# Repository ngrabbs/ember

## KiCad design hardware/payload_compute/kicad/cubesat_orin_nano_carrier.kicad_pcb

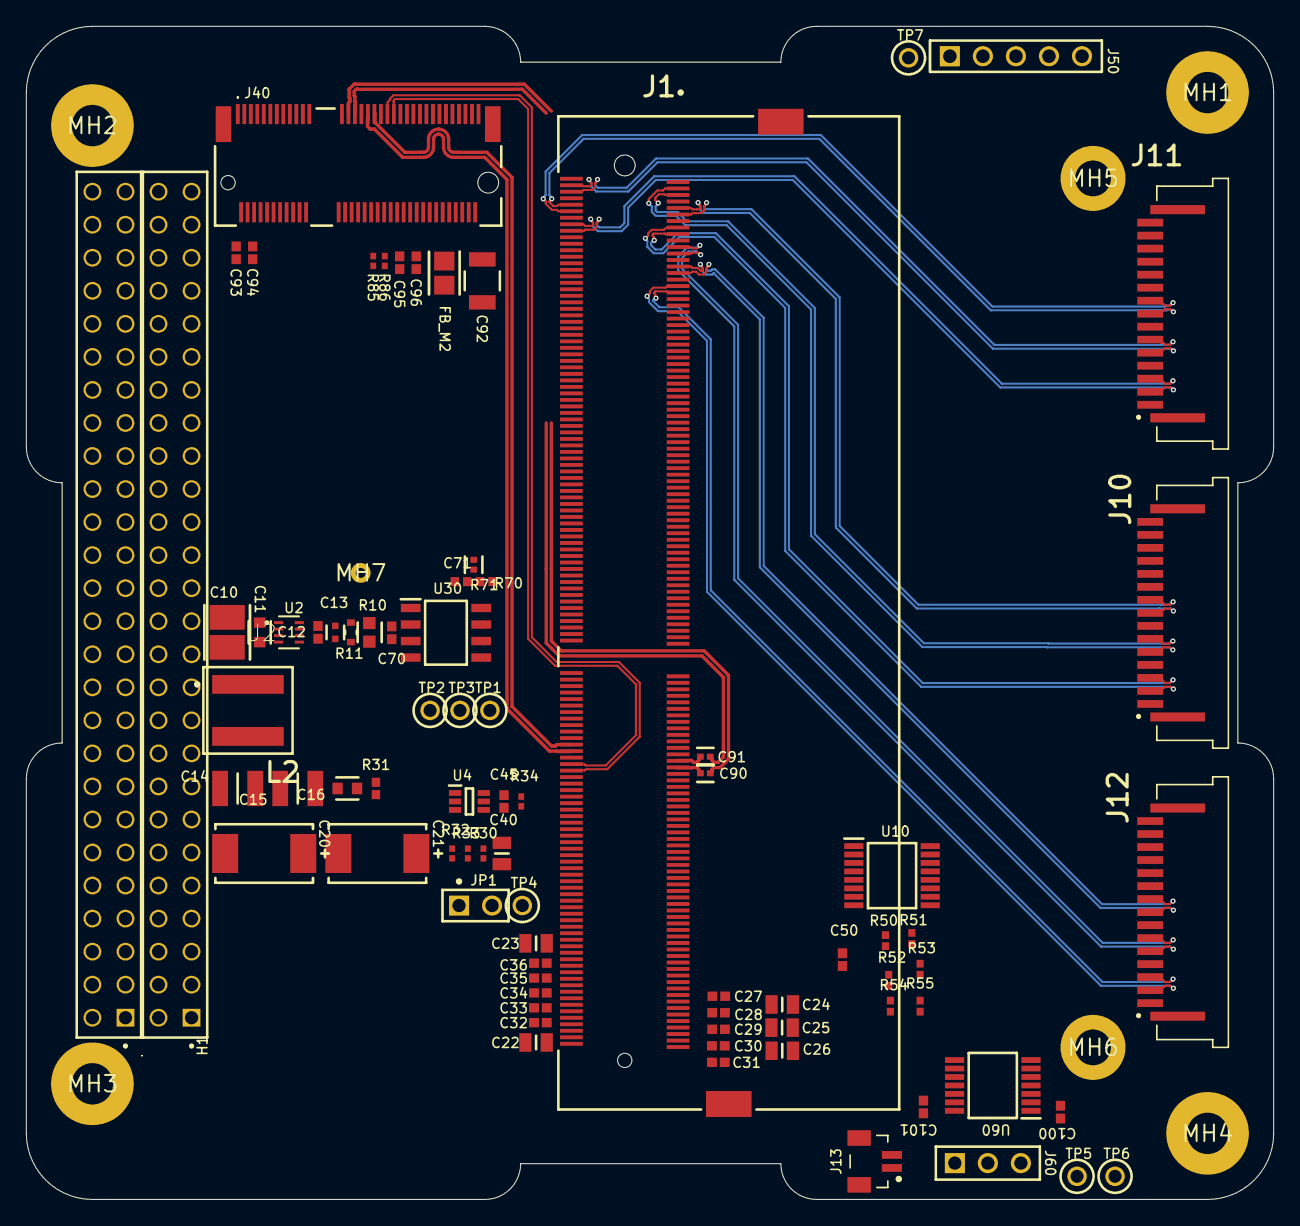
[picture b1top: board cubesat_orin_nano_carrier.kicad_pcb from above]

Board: 4 copper layers, 95.9 x 90.2 mm, 87 parts (0 on the bottom side), 86 nets.

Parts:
C10: GCM32EC7YA106KA03L; FP-GCM32E-0_3-IPC_B
C11, C16: C14663; FP-CC0603-DA-MFG
C12, C27, C28, C29, C30, C31, C32, C33, C34, C35, C36, C45, C50, C70, C93, C94, C95, C96, C100, C101: CL05B104KO5NNNC; CAPC1050X55X23ML05T13
C13: CC0402KRX7R7BB333; FP-CC0402-MFG
C14, C15: CL32A226KAJNNNE; CAPC3225X270N
C20, C21: TAJD107K020RNJ; FP-TAJD-MFG
C22, C23, C24, C25, C26, C40: CL21B106KPQNNNE; CAPC2012X140N
C71: CL05B472KB5NNNC; FP-CL967-IPC_C
C90, C91: CL05B224KO5NNNC; FP-CL549-IPC_C
C92: GRM32ER71E226KE15L; FP-GRM32E-0_3-0_2-MFG
FB_M2: BLM21PG600SN1D; FP-BLM21-0_2-t0_85-e0_5-d-IPC_A
H1, H2: ESQ-126-39-G-D; SAMTEC_ESQ-126-39-G-D
J1: 2309413-1; FP-2309413-1-MFG
J10, J11, J12: SFW15R-2STE1LF; AMPHENOL_SFW15R-2STE1LF
J13: BM02B-SRSS-TB(LF)(SN); BM02B-SRSS-TB_LF_SN_MFG
J40: MDT420E01001
J50: SSW-105-01-T-S; SMTC-SSW-105-01-X-S
J60: TSW-103-07-F-S; SMTC-TSW-103-07-X-S
JP1: 68000-102HLF; AMPH-68000-102HLF_V
L2: 74439346068; WE-XHMI_6060
MH1, MH2, MH3, MH4: M3_PC104_3.18mm
MH5, MH6: M2.5_module_2.75mm
MH7: Tooling_0.762mm
R10: CRCW060352K3FKEA; FP-CRCW0603-e3-IPC_B
R11: SG73P1JTTD1002F; FP-SG73P1J-MFG
R30, R32, R33, R34, R85, R86: RC0402FR-0710KL; RESC1005X40X25LL05T10
R31: RC0402FR-0749K9L; RESC1005X40X25ML05T10
R50, R51, R52, R53, R54, R55: RC0402FR-074K7L; RESC1005X40X25NL05T10
R70, R71: RC0402FR-0760R4L; RESC1005X40X25ML05T10
TP1, TP2, TP3, TP4, TP5, TP6, TP7: 5003; KSTN-5003
U2: TPS62933FDRLR; SOT5X3-8_DRL_TEX
U4: 74LVC2G07GW,125; SOP65P210X110-6N
U10: PCA9546APW,118; SOP65P640X110-16N
U30: TCAN332GDR; SOIC127P600X175-8N
U60: TXB0104QPWRQ1; SOP65P640X120-14N

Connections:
+1V8_MOD: C45.2, C100.1, R32.2, R33.1, U4.5, U60.1
+3V3: C50.2, C70.2, C101.1, FB_M2.1, H2.27, H2.28, J10.15, J11.15, J12.15, R34.1, R50.2, R51.2, R52.2, R53.2, R54.2, R55.2, U10.16, U30.3, U60.8, U60.14
+3V3_M2: C92.1, C93.2, C94.2, C95.2, C96.2, FB_M2.2, R85.1, R86.1
+5V: H2.25, H2.26
+5V_ORIN: C14.1, C15.1, C16.1, C20.2, C21.2, C22.2, C23.2, C24.2, C25.2, C26.2, C27.2, C28.2, C29.2, C30.2, C31.2, C32.2, C33.2, C34.2, C35.2, C36.2, J1.251, J1.252, J1.253, J1.254, J1.255, J1.256, J1.257, J1.258, J1.259, J1.260, L2.2, R10.2, R30.1, R31.2
+5V_TEST: J50.1, TP7.1
CAM0_CLK_N: J1.10, J10.8
CAM0_CLK_P: J1.12, J10.9
CAM0_D0_N: J1.4, J10.5
CAM0_D0_P: J1.6, J10.6
CAM0_D1_N: J1.16, J10.2
CAM0_D1_P: J1.18, J10.3
CAM0_PWDN: J1.127, J10.11
CAM0_SCL: J10.13, R51.1, U10.5
CAM0_SDA: J10.14, R50.1, U10.4
CAM1_CLK_N: J1.9, J11.8
CAM1_CLK_P: J1.11, J11.9
CAM1_D0_N: J1.3, J11.5
CAM1_D0_P: J1.5, J11.6
CAM1_D1_N: J1.15, J11.2
CAM1_D1_P: J1.17, J11.3
CAM1_PWDN: J1.130, J11.11
CAM1_SCL: J11.13, R53.1, U10.7
CAM1_SDA: J11.14, R52.1, U10.6
CAM2_CLK_N: J1.28, J12.8
CAM2_CLK_P: J1.30, J12.9
CAM2_D0_N: J1.22, J12.5
CAM2_D0_P: J1.24, J12.6
CAM2_D1_N: J1.34, J12.2
CAM2_D1_P: J1.36, J12.3
CAM2_PWDN: J1.211, J12.11
CAM2_SCL: J12.13, R54.1, U10.10
CAM2_SDA: J12.14, R55.1, U10.9
CAM_I2C_SCL: J1.213, U10.14
CAM_I2C_SDA: J1.215, U10.15
CAM_TRIG_1V8: J1.128, J13.1
CAN_H: H1.51, R70.2, U30.7
CAN_L: H1.52, R71.1, U30.6
CAN_RX: J1.143, U30.4
CAN_TX: J1.145, U30.1
CLK_32K_OUT: J1.210, TP3.1
DBG_UART_RX_1V8: J1.205, TP6.1, U60.3
DBG_UART_RX_3V3: J60.3, U60.12
DBG_UART_TX_1V8: J1.203, TP5.1, U60.2
DBG_UART_TX_3V3: J60.2, U60.13
FRC_RCVRY_N: J1.214, JP1.1, R33.2
GND: C10.2, C11.2, C13.2, C14.2, C15.2, C16.2, C20.1, C21.1, C22.1, C23.1, C24.1, C25.1, C26.1, C27.1, C28.1, C29.1, C30.1, C31.1, C32.1, C33.1, C34.1, C35.1, C36.1, C40.1, C45.1, C50.1, C70.1, C71.2, C92.2, C100.2, C101.2, H2.29, H2.30, H2.31, H2.32, J1.1, J1.2, J1.7, J1.8, J1.13, J1.14, J1.19, J1.20, J1.25, J1.26, J1.31, J1.32, J1.37, J1.38, J1.43, J1.44, J1.49, J1.50, J1.55, J1.56, J1.61, J1.62, J1.67, J1.68, J1.73, J1.74, J1.79, J1.80, J1.85, J1.86, J1.102, J1.107, J1.119, J1.125, J1.129, J1.132, J1.135, J1.138, J1.141, J1.144, J1.146, J1.147, J1.152, J1.153, J1.158, J1.159, J1.164, J1.165, J1.170, J1.171, J1.176, J1.177, J1.200, J1.201, J1.217, J1.231, J1.241, J1.242, J1.243, J1.244, J1.245, J1.246, J1.247, J1.248, J1.249, J1.250, J10.1, J10.4, J10.7, J10.10, J10.S1, J10.S2, J11.1, J11.4, J11.7, J11.10, J11.S1, J11.S2, J12.1, J12.4, J12.7, J12.10, J12.S1, J12.S2, J13.2, J13.3, J13.4, J40.76, J40.77, J50.5, J60.1, JP1.2, MH1.3, MH2.4, MH3.1, MH4.2, MH5.5, MH6.5, R11.1, R31.1, U2.4, U4.2, U10.1, U10.2, U10.8, U10.13, U30.2, U60.7
I2C_SCL: H1.43, J1.185
I2C_SDA: H1.41, J1.187
M2_PCIE1_TX0_N: C91.2, J40.37
M2_PCIE1_TX0_P: C90.2, J40.35
MOD_SLEEP_N: J1.178, TP2.1
MUX_RST_N_1V8: J1.206, U4.3
MUX_RST_N_3V3: R34.2, U4.4, U10.3
NetC12_1: C12.1, U2.6
NetC12_2: C12.2, L2.1, U2.5
NetC13_1: C13.1, U2.7
NetC71_1: C71.1, R70.1, R71.2
NetC93_1: C93.1, J40.2
NetC94_1: C94.1, J40.4
NetC95_1: C95.1, J40.72
NetC96_1: C96.1, J40.74
NetJ40_54: J40.54, R85.2
NetJ40_56: J40.56, R86.2
NetR10_1: R10.1, R11.2, U2.8
PAYLOAD_EN: H1.50, U2.2
PAYLOAD_FAULT_N: H2.47, TP4.1, U4.6
PAYLOAD_SLEEP_REQ_N: H2.48, J1.240
PCIE1_CLKREQ*: J1.182, J40.53
PCIE1_CLK_N: J1.173, J40.49
PCIE1_CLK_P: J1.175, J40.47
PCIE1_RST*: J1.183, J40.52
PCIE1_RX0_N: J1.167, J40.43
PCIE1_RX0_P: J1.169, J40.41
PCIE1_TX0_N: C91.1, J1.172
PCIE1_TX0_P: C90.1, J1.174
PCIE_WAKE*: J1.179, J40.55
PWR_EN: C40.2, J1.237, R30.2
SHDN_REQ_N: J1.233, U4.1
SYS_RESET_N: J1.239, R32.1, TP1.1
USB0_D_N: J1.109, J50.2
USB0_D_P: J1.111, J50.3
USB0_VBUS_DET: J1.87, J50.4
USB1_D_N: J1.115, J40.5
USB1_D_P: J1.117, J40.3
VBAT: C10.1, C11.1, H2.45, H2.46, U2.3

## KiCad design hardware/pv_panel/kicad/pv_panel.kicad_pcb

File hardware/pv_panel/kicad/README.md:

# PV panel Rev D — KiCad

Open `pv_panel.kicad_pro` with KiCad 10. The project contains the recovered
schematic, routed PCB, project-local footprint libraries, and solar-module
STEP model. Diode and connector models are embedded in the board and footprints.

The recovered schematic follows the routed PCB's six nets and eleven named
components. The original free pads and mounting holes remain board-only items.
Footprints are linked to the recovered symbols; their placed geometry is retained
in individual project-local library variants.

## Onshape exports

- `exports/pv_panel_rev_D_presentation.step` includes colored components, solar-cell
  detail, copper, pads, soldermask, and silkscreen.
- `exports/pv_panel_rev_D_mechanical.step` provides simpler board/component geometry.

Both files use millimeters and a board-centered XY origin. They reopen as valid
OpenCascade shapes; an actual Onshape import has not been tested.

## Geometry and assumptions

- Board outline: nominally 82.5 × 98 mm, with the original rounded corners.
- Mounting holes: four 3 mm drills at the original positions, spaced 76.2 × 91.6 mm.
- Board thickness: 0.41116 mm from the original layer stack. Confirm against
  physical hardware for precise fitting.
- Solar modules: nominal 70 × 23 × 1.2 mm bodies based on the
  [ANYSOLAR product table](https://anysolar.biz/products/gen3/), with an assumed
  0.15 mm stand-off. Surface detail is illustrative; dimensions represent nominal
  geometry rather than a tolerance envelope.
- Original diode and connector bodies are retained as package representations;
  their geometry has not been certified against the fitted manufacturers' drawings.
- Screws, mating cables, and solder fillets are not modeled.
- D1, the through-hole diode, is mounted on the outside solar-cell face (F.Cu).
  The connector and surface-mount diodes remain on the inside face (B.Cu).
  Its legacy 3D body is raised by a 1 mm model Z offset to clear the nearest solar
  module. This is an assembly-height assumption to confirm against hardware;
  both diode holes and their net assignments are unchanged.

## Recovery changes

Removed zero-length outline segments, repaired PV2 pad 1's net assignment,
restored the original 10 mil zone clearance, refilled the ground zones, removed
isolated copper and a tiny dangling track stub, and corrected through-hole paste
settings and silkscreen collisions. Corner copper rings were reduced from 6.4 mm
to 5 mm to satisfy the existing 0.5 mm edge-clearance rule; drill diameters,
mounting centers, and the outline are unchanged.

The native schematic import had scale and connectivity defects, so the working
schematic was reconstructed with standard KiCad symbols and checked against the
PCB pin connectivity. The archived sources disagree on diode population: the
older drawing omits D1 and labels CR1–CR5 as RBR1MM60ATR, while the PCB includes
D1=SB140 and labels CR1–CR5 as STPS1L30MF. This project follows the PCB. Confirm
the intended/fitted diode part numbers before fabrication.

## Validation

The saved project passes KiCad DRC, ERC, and schematic parity with zero findings.
All six nets match pin-for-pin across the eleven named components. Both STEP
exports contain valid CAD shapes (58 solids for mechanical, 129 for presentation),
and top/bottom renders were visually inspected. These checks cover the recovered
design and mockup export; hardware qualification remains a separate activity.

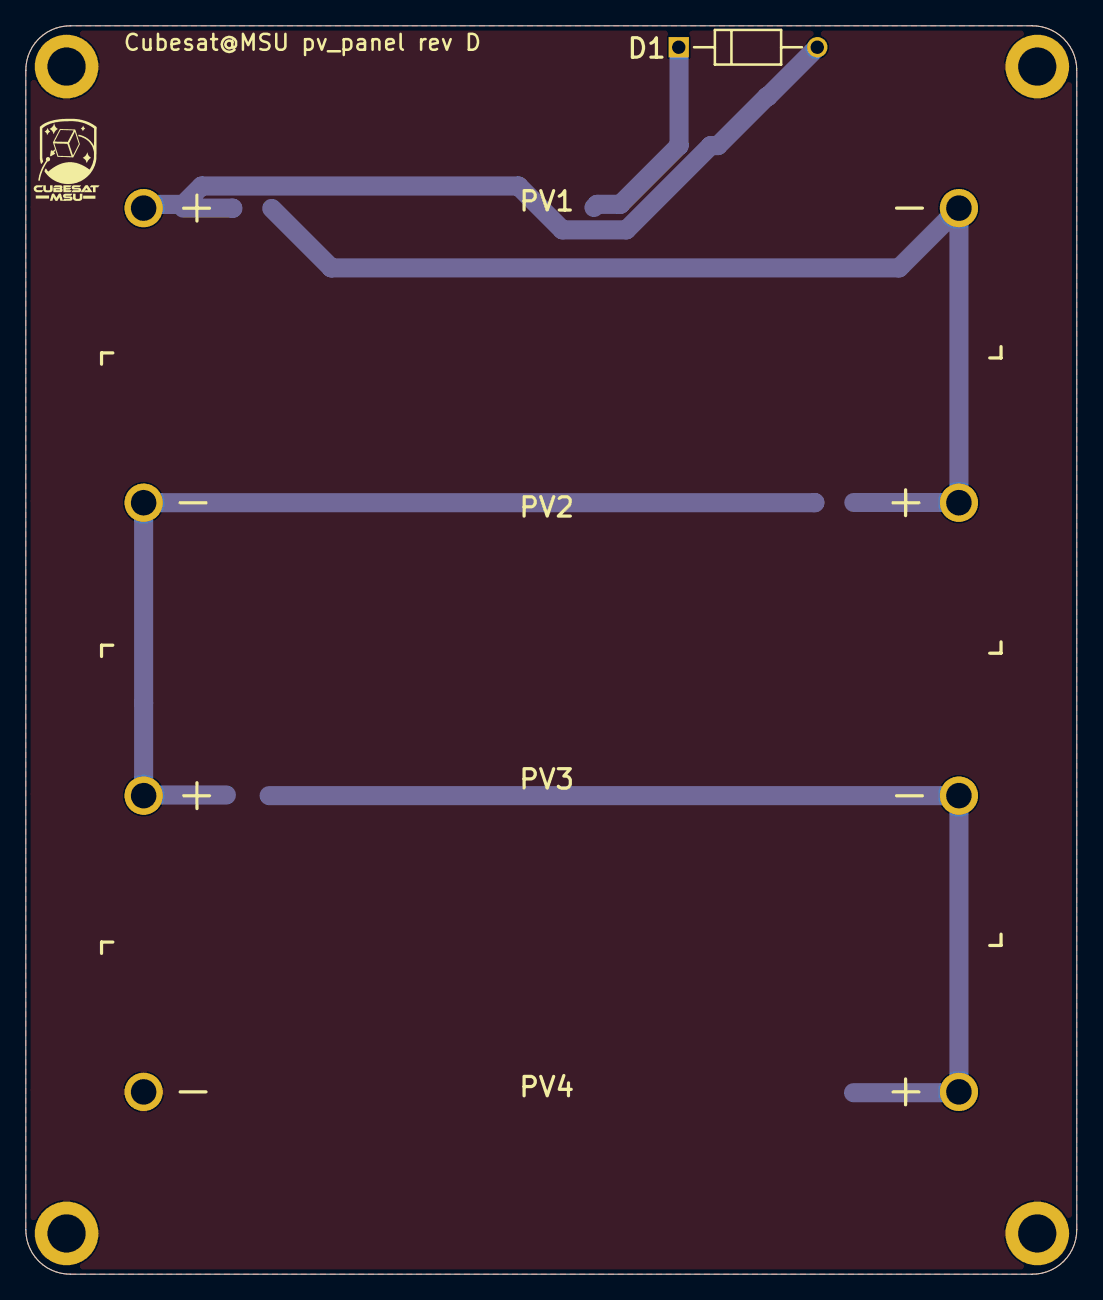
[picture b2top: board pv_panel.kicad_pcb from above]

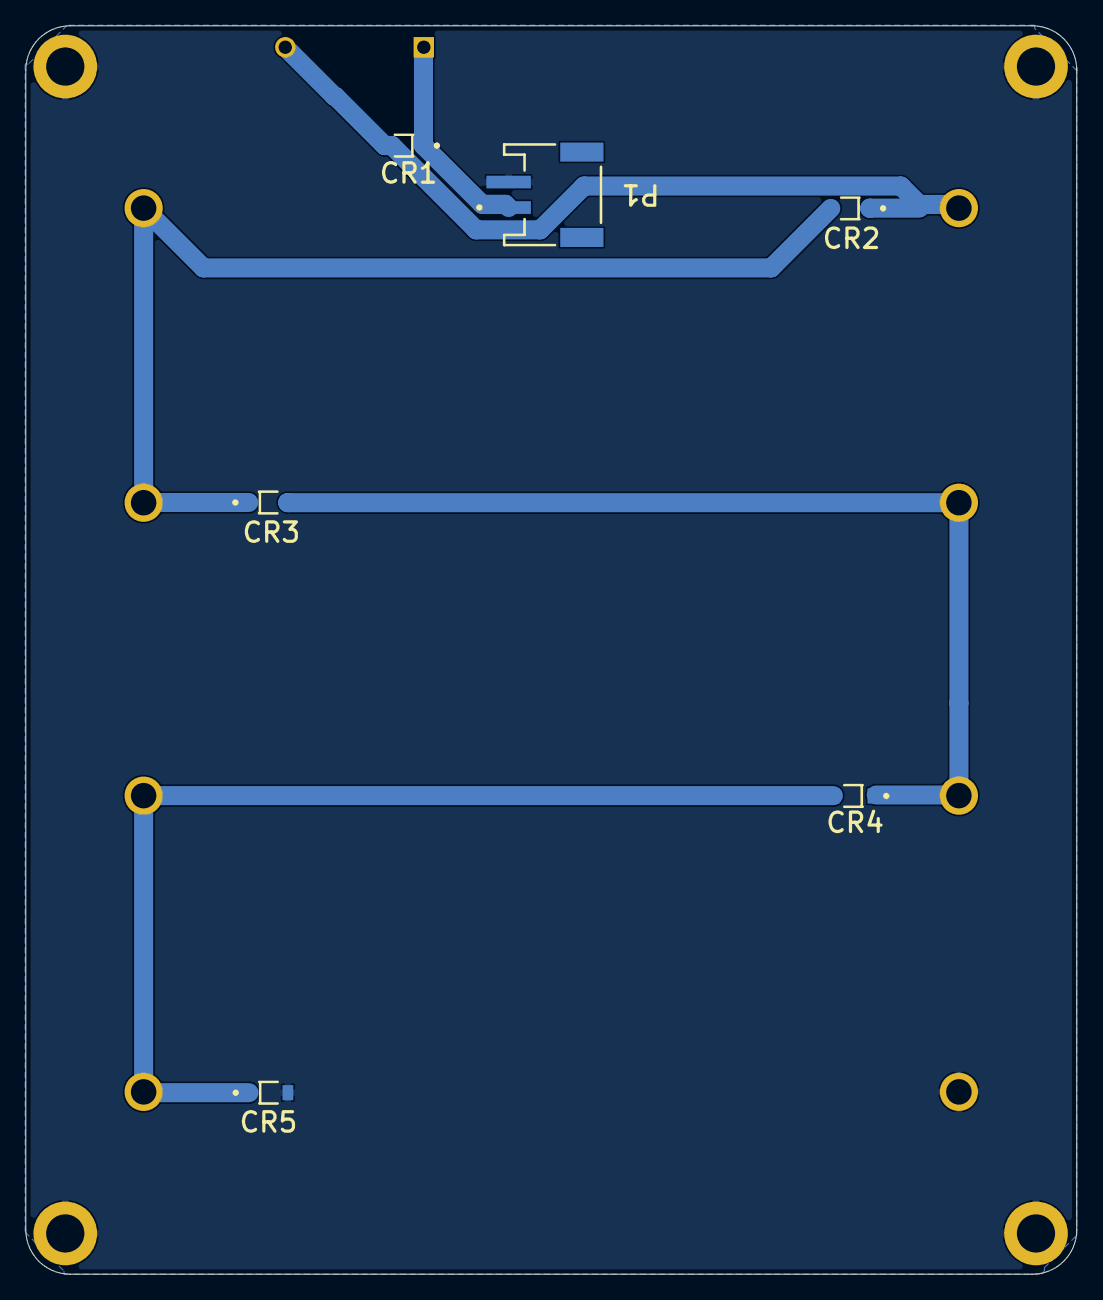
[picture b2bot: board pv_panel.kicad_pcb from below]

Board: 2 copper layers, 82.5 x 98.0 mm, 11 parts (6 on the bottom side), 6 nets.

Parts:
CR1: STPS1L30MF; FP-PMDU-MFG_RevD_CR1
CR2: STPS1L30MF; FP-PMDU-MFG_RevD_CR2
CR3: STPS1L30MF; FP-PMDU-MFG_RevD_CR3
CR4: STPS1L30MF; FP-PMDU-MFG_RevD_CR4
CR5: STPS1L30MF; FP-PMDU-MFG_RevD_CR5
D1: SB140; FP-017AH-MFG_RevD_D1
P1: S2B-PH-SM4-TB(LF)(SN); JST- S2B-PH-SM4-TB(LF)(SN)-2_V_RevD_P1
PV1: SM141K10TF; SM141K10TF_RevD_PV1
PV2: SM141K10TF; SM141K10TF_RevD_PV2
PV3: SM141K10TF; SM141K10TF_RevD_PV3
PV4: SM141K10TF; SM141K10TF_RevD_PV4

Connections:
/NetCR1_2: CR1.2, CR2.1, D1.2, PV1.1
/NetCR2_2: CR2.2, CR3.1, PV1.2, PV2.1
/NetCR3_2: CR3.2, CR4.1, PV2.2, PV3.1
/NetCR4_2: CR4.2, CR5.1, PV3.2, PV4.1
GND: CR5.2, P1.2, PV4.2
VCC: CR1.1, D1.1, P1.1
